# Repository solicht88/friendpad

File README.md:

# friendpad
My first ever PCB, created for Hack Club's YSWS [Hackpad](https://hackpad.hackclub.com/)!  
Designed to be used for 4 key rhythm games, as well as have enough keys to be used for shortcuts or as a midi controller.  
There was an attempt to make something resembling a friendly face by placing rotary encoders (eyes) on both sides of the OLED (mouth).  

### Acknowledgements:  
[KiCad](https://www.kicad.org/)  
[Shapr3D](https://www.shapr3d.com/)  
[ScottoKeebs Kicad Footprint Collection](https://github.com/joe-scotto/scottokeebs/tree/main/Extras/ScottoKicad)

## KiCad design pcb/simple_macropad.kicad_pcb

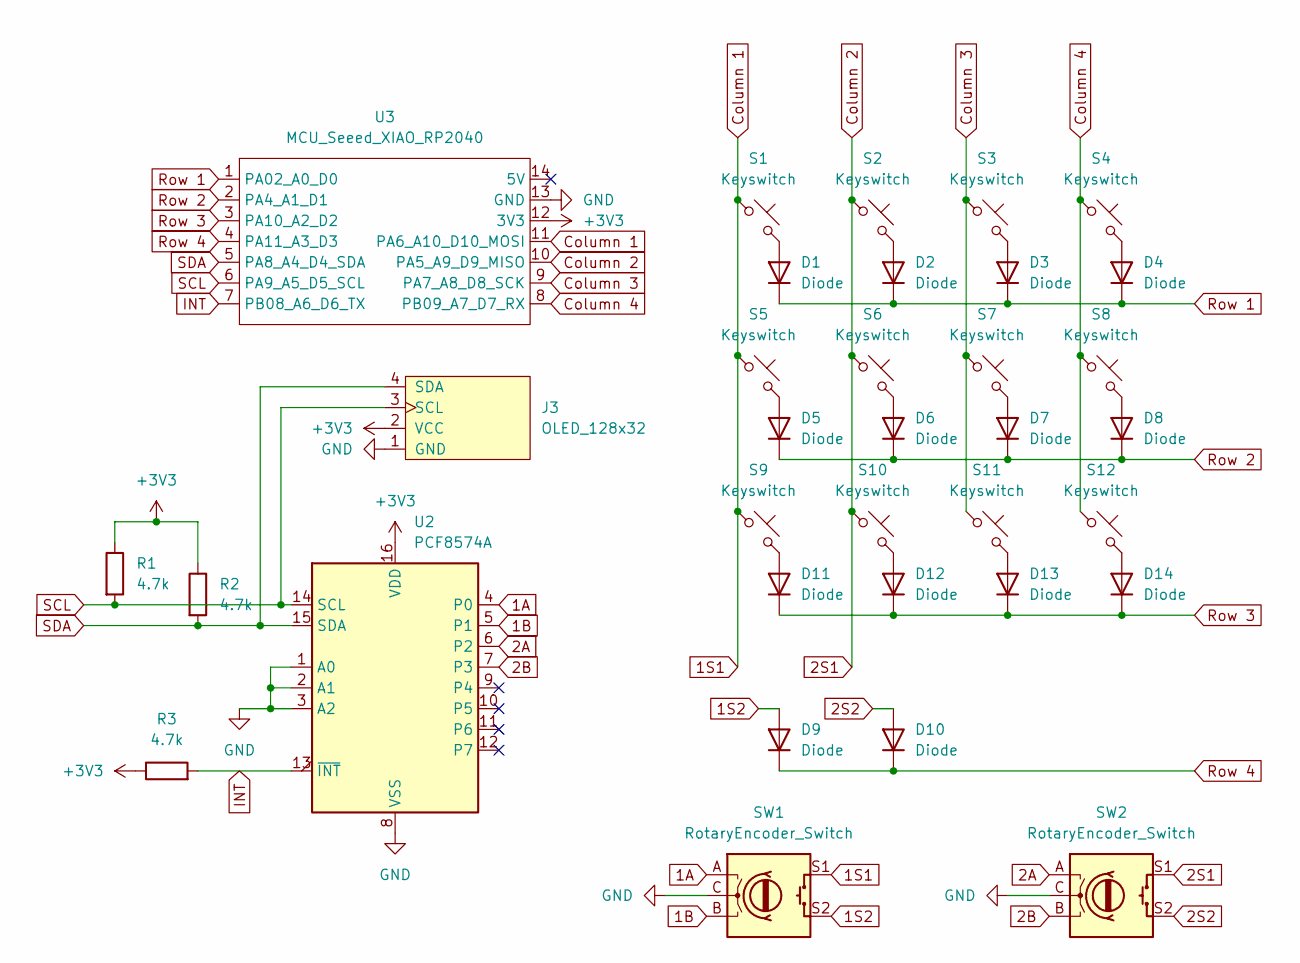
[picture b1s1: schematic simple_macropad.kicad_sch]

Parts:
D1, D2, D3, D4, D5, D6, D7, D8, D9, D10, D11, D12, D13, D14: Diode; Diode_DO-35
J3: OLED_128x32
R1, R2, R3: 4.7k; R_Axial_DIN0207_L6.3mm_D2.5mm_P10.16mm_Horizontal
S1, S2, S3, S4, S5, S6, S7, S8, S9, S10, S11, S12: Keyswitch; MX_PCB_1.00u
SW1, SW2: RotaryEncoder_Switch; RotaryEncoder_Alps_EC11E_Vertical_H20mm
U2: PCF8574A; DIP-16_W7.62mm
U3: MCU_Seeed_XIAO_RP2040; Seeed_XIAO_RP2040

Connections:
1A: SW1.A, U2.4 (P0)
1B: SW1.B, U2.5 (P1)
1S1: S1.1, S5.1, S9.1, SW1.S1, U3.11 (PA6_A10_D10_MOSI)
1S2: D9.2 (A), SW1.S2
2A: SW2.A, U2.6 (P2)
2B: SW2.B, U2.7 (P3)
2S1: S2.1, S6.1, S10.1, SW2.S1, U3.10 (PA5_A9_D9_MISO)
2S2: D10.2 (A), SW2.S2
+3V3: J3.2 (VCC), R1.1, R2.1, R3.1, U2.16 (VDD), U3.12 (3V3)
Column 3: S3.1, S7.1, S11.1, U3.9 (PA7_A8_D8_SCK)
Column 4: S4.1, S8.1, S12.1, U3.8 (PB09_A7_D7_RX)
GND: J3.1 (GND), SW1.C, SW2.C, U2.1 (A0), U2.2 (A1), U2.3 (A2), U2.8 (VSS), U3.13 (GND)
INT: R3.2, U2.13 (~INT), U3.7 (PB08_A6_D6_TX)
unnamed: D1.2 (A), S1.2
unnamed: D2.2 (A), S2.2
unnamed: D3.2 (A), S3.2
unnamed: D4.2 (A), S4.2
unnamed: D5.2 (A), S5.2
unnamed: D6.2 (A), S6.2
unnamed: D7.2 (A), S7.2
unnamed: D8.2 (A), S8.2
unnamed: D11.2 (A), S9.2
unnamed: D12.2 (A), S10.2
unnamed: D13.2 (A), S11.2
unnamed: D14.2 (A), S12.2
Row 1: D1.1 (K), D2.1 (K), D3.1 (K), D4.1 (K), U3.1 (PA02_A0_D0)
Row 2: D5.1 (K), D6.1 (K), D7.1 (K), D8.1 (K), U3.2 (PA4_A1_D1)
Row 3: D11.1 (K), D12.1 (K), D13.1 (K), D14.1 (K), U3.3 (PA10_A2_D2)
Row 4: D9.1 (K), D10.1 (K), U3.4 (PA11_A3_D3)
SCL: J3.3 (SCL), R1.2, U2.14 (SCL), U3.6 (PA9_A5_D5_SCL)
SDA: J3.4 (SDA), R2.2, U2.15 (SDA), U3.5 (PA8_A4_D4_SDA)

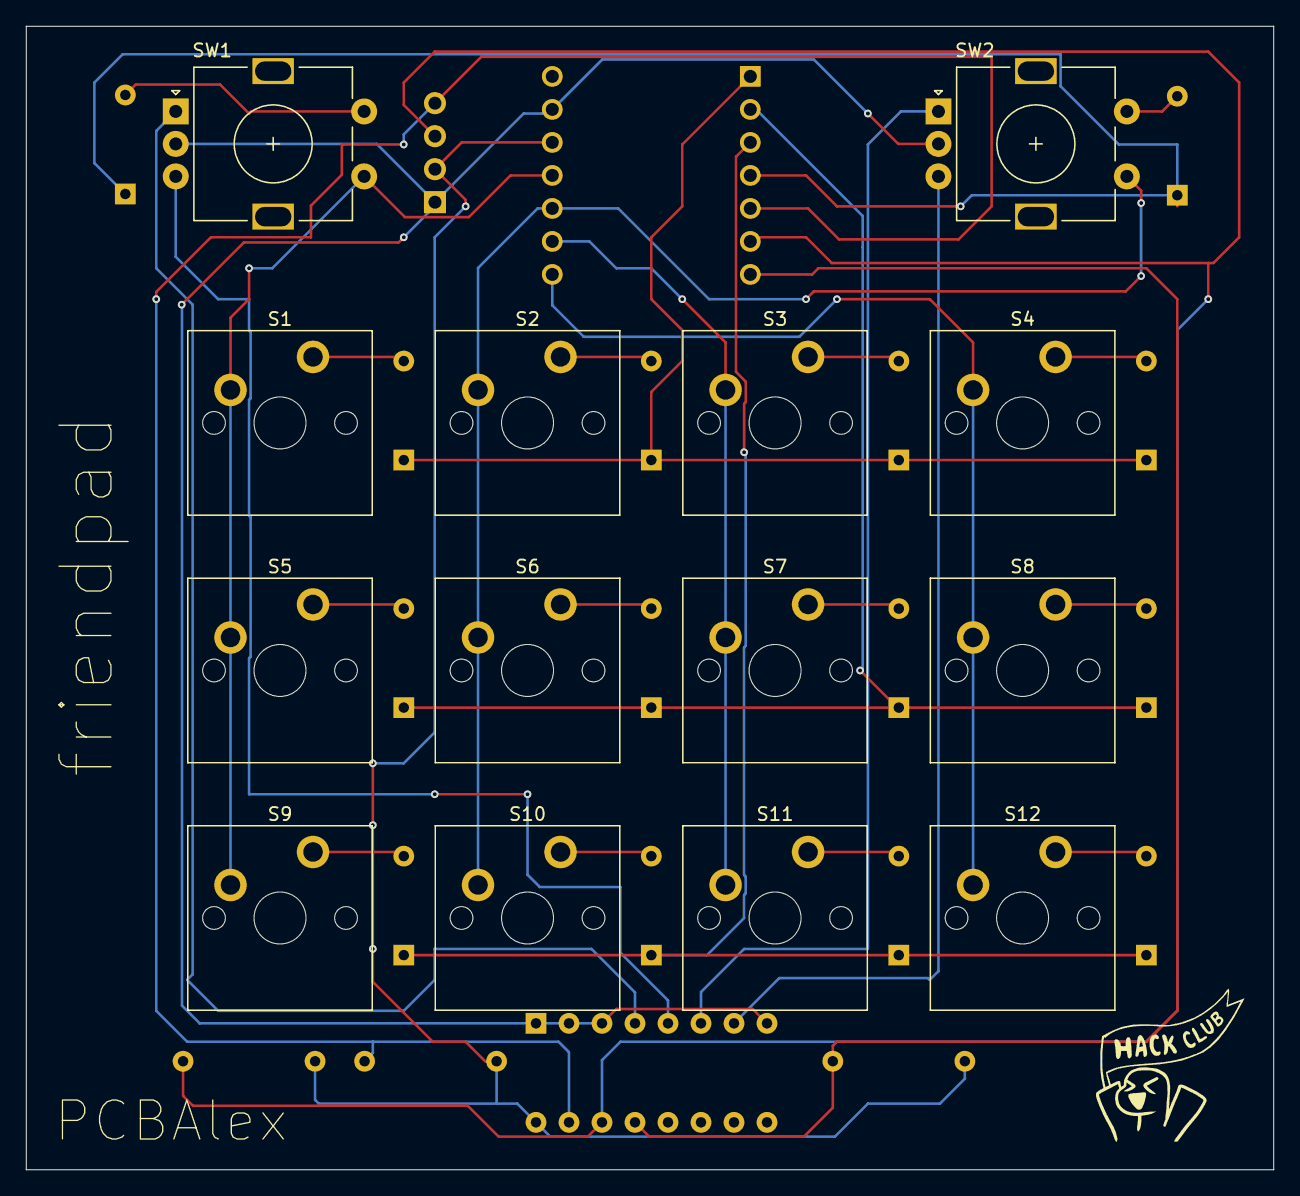
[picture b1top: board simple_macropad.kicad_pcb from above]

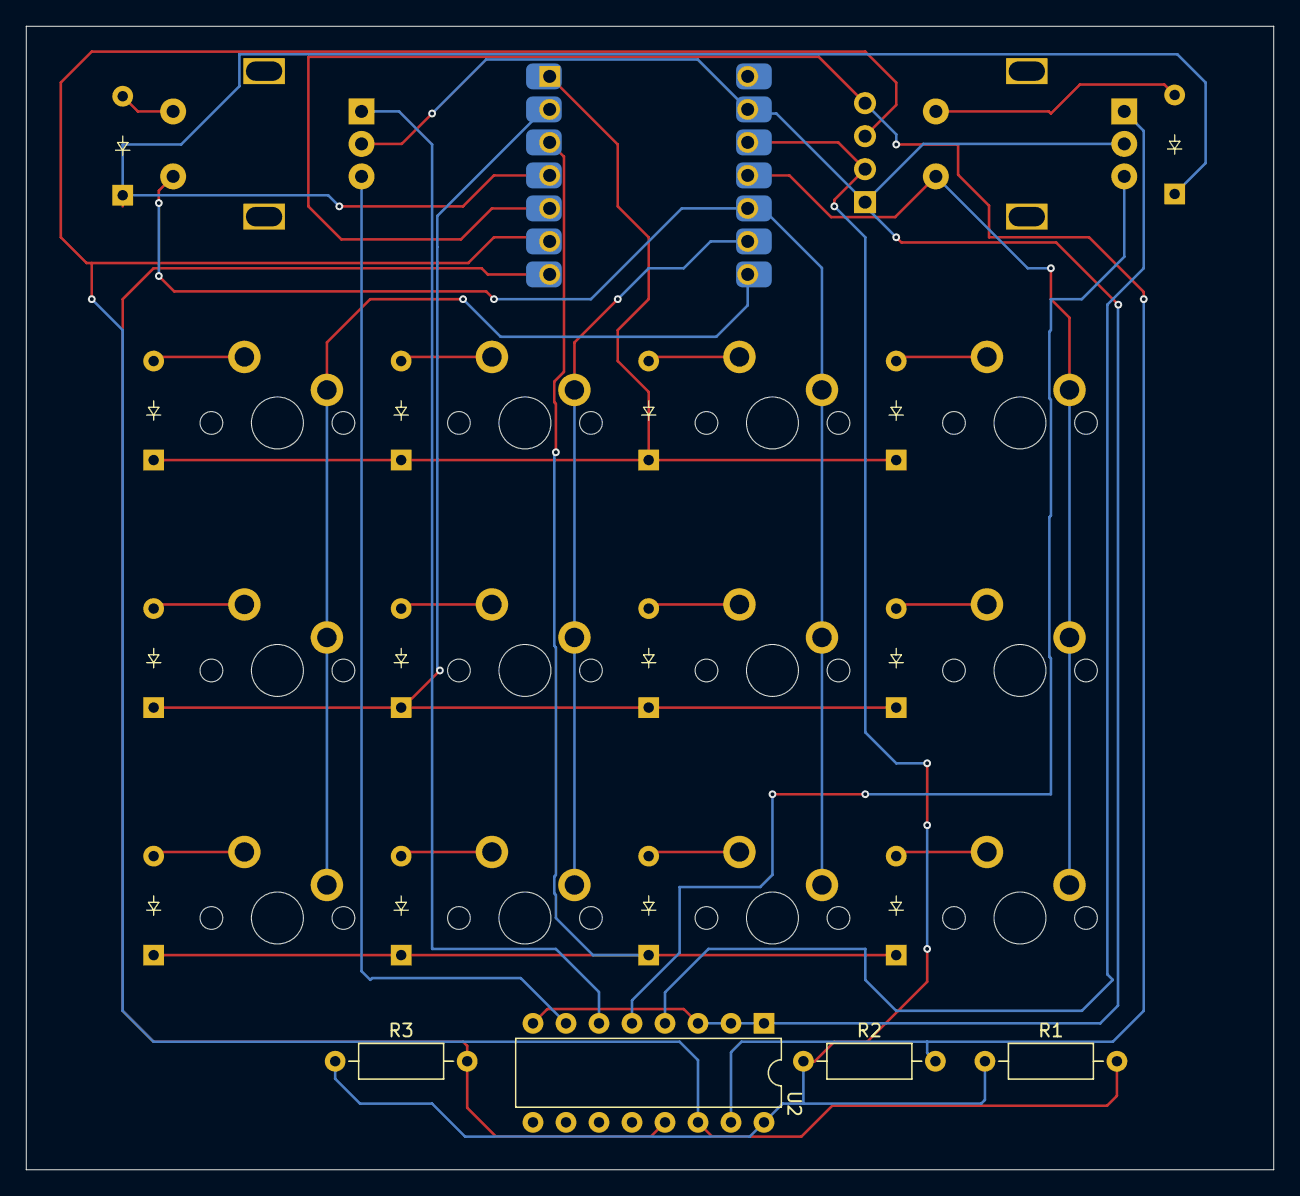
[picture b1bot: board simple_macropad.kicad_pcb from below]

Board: 2 copper layers, 96.0 x 88.0 mm, 35 parts (19 on the bottom side), 31 nets.

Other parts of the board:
 : LOGO

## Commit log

2024-10-08 created keyswitch matrix
2024-10-18 added footprints
2024-10-20 wired components in pcb
2024-10-20 completed case stl files
2024-10-21 created firmware
2024-10-21 updated pcb silkscreen
2024-10-22 update readme, bom, and cad
2024-10-22 created gerbers.zip, updated .stl files
